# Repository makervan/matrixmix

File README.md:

# MatrixMix

Matrix mixer. Currently only 4 inputs, 4 outputs, passive. Option for passthrough sync. There's an extension port to chain mulitple mixers together, for more inputs, or add a separate amplifer for the outputs.

## License
Created by Severin Schols, and shared under CC-BY-SA-4.0. See LICENSE for more information.

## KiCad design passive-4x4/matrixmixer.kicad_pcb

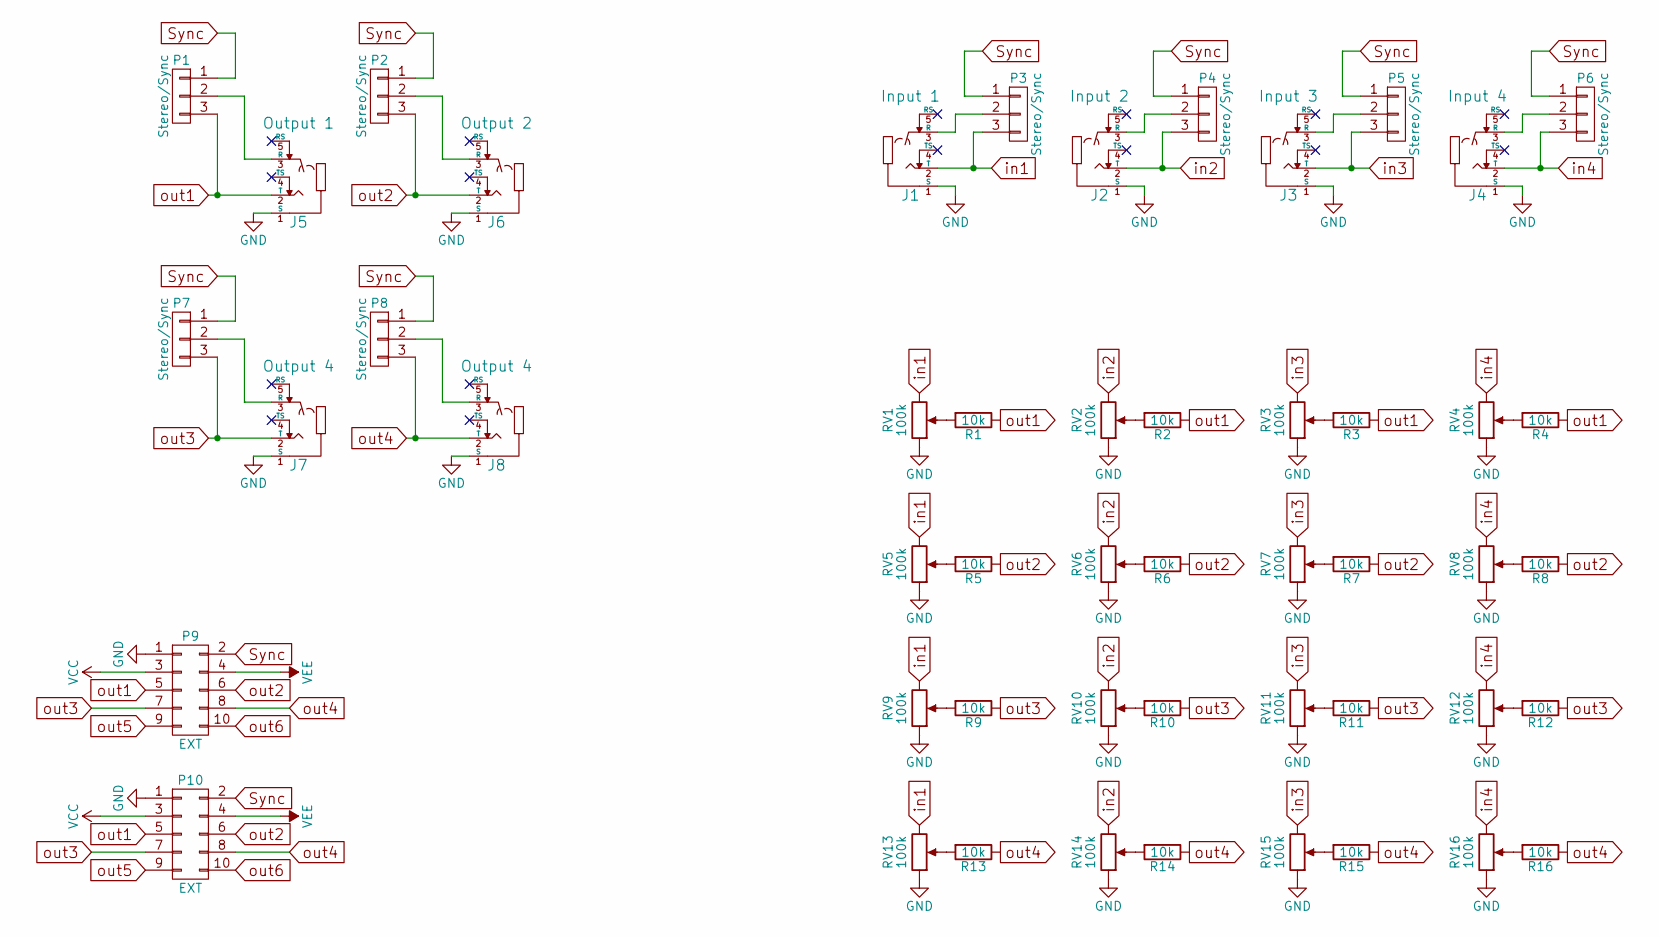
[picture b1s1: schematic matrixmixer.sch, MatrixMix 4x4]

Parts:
J1: Input 1; AudioJack3.5mm
J2: Input 2; AudioJack3.5mm
J3: Input 3; AudioJack3.5mm
J4: Input 4; AudioJack3.5mm
J5: Output 1; AudioJack3.5mm
J6: Output 2; AudioJack3.5mm
J7, J8: Output 4; AudioJack3.5mm
P1, P2, P3, P4, P5, P6, P7, P8: Stereo/Sync; Pin_Header_Straight_1x03
P9, P10: EXT; Pin_Header_Angled_2x05
R1, R2, R3, R4, R5, R6, R7, R8, R9, R10, R11, R12, R13, R14, R15, R16: 10k; Resistor_Horizontal_RM10mm
RV1, RV2, RV3, RV4, RV5, RV6, RV7, RV8, RV9, RV10, RV11, RV12, RV13, RV14, RV15, RV16: 100k; Potentiometer_Alpha-RV09

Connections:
GND: J1.1 (S), J2.1 (S), J3.1 (S), J4.1 (S), J5.1 (S), J6.1 (S), J7.1 (S), J8.1 (S), P9.1, P10.1, RV1.1, RV2.1, RV3.1, RV4.1, RV5.1, RV6.1, RV7.1, RV8.1, RV9.1, RV10.1, RV11.1, RV12.1, RV13.1, RV14.1, RV15.1, RV16.1
unnamed: J1.3 (R), P3.2
unnamed: J2.3 (R), P4.2
unnamed: J3.3 (R), P5.2
unnamed: J4.3 (R), P6.2
unnamed: J5.3 (R), P1.2
unnamed: J6.3 (R), P2.2
unnamed: J7.3 (R), P7.2
unnamed: J8.3 (R), P8.2
unnamed: R1.2, RV1.2
unnamed: R2.2, RV2.2
unnamed: R3.2, RV3.2
unnamed: R4.2, RV4.2
unnamed: R5.2, RV5.2
unnamed: R6.2, RV6.2
unnamed: R7.2, RV7.2
unnamed: R8.2, RV8.2
unnamed: R9.2, RV9.2
unnamed: R10.2, RV10.2
unnamed: R11.2, RV11.2
unnamed: R12.2, RV12.2
unnamed: R13.2, RV13.2
unnamed: R14.2, RV14.2
unnamed: R15.2, RV15.2
unnamed: R16.2, RV16.2
Sync: P1.1, P2.1, P3.1, P4.1, P5.1, P6.1, P7.1, P8.1, P9.2, P10.2
VCC: P9.3, P10.3
VEE: P9.4, P10.4
in1: J1.2 (T), P3.3, RV1.3, RV5.3, RV9.3, RV13.3
in2: J2.2 (T), P4.3, RV2.3, RV6.3, RV10.3, RV14.3
in3: J3.2 (T), P5.3, RV3.3, RV7.3, RV11.3, RV15.3
in4: J4.2 (T), P6.3, RV4.3, RV8.3, RV12.3, RV16.3
out1: J5.2 (T), P1.3, P9.5, P10.5, R1.1, R2.1, R3.1, R4.1
out2: J6.2 (T), P2.3, P9.6, P10.6, R5.1, R6.1, R7.1, R8.1
out3: J7.2 (T), P7.3, P9.7, P10.7, R9.1, R10.1, R11.1, R12.1
out4: J8.2 (T), P8.3, P9.8, P10.8, R13.1, R14.1, R15.1, R16.1
out5: P9.9, P10.9
out6: P9.10, P10.10

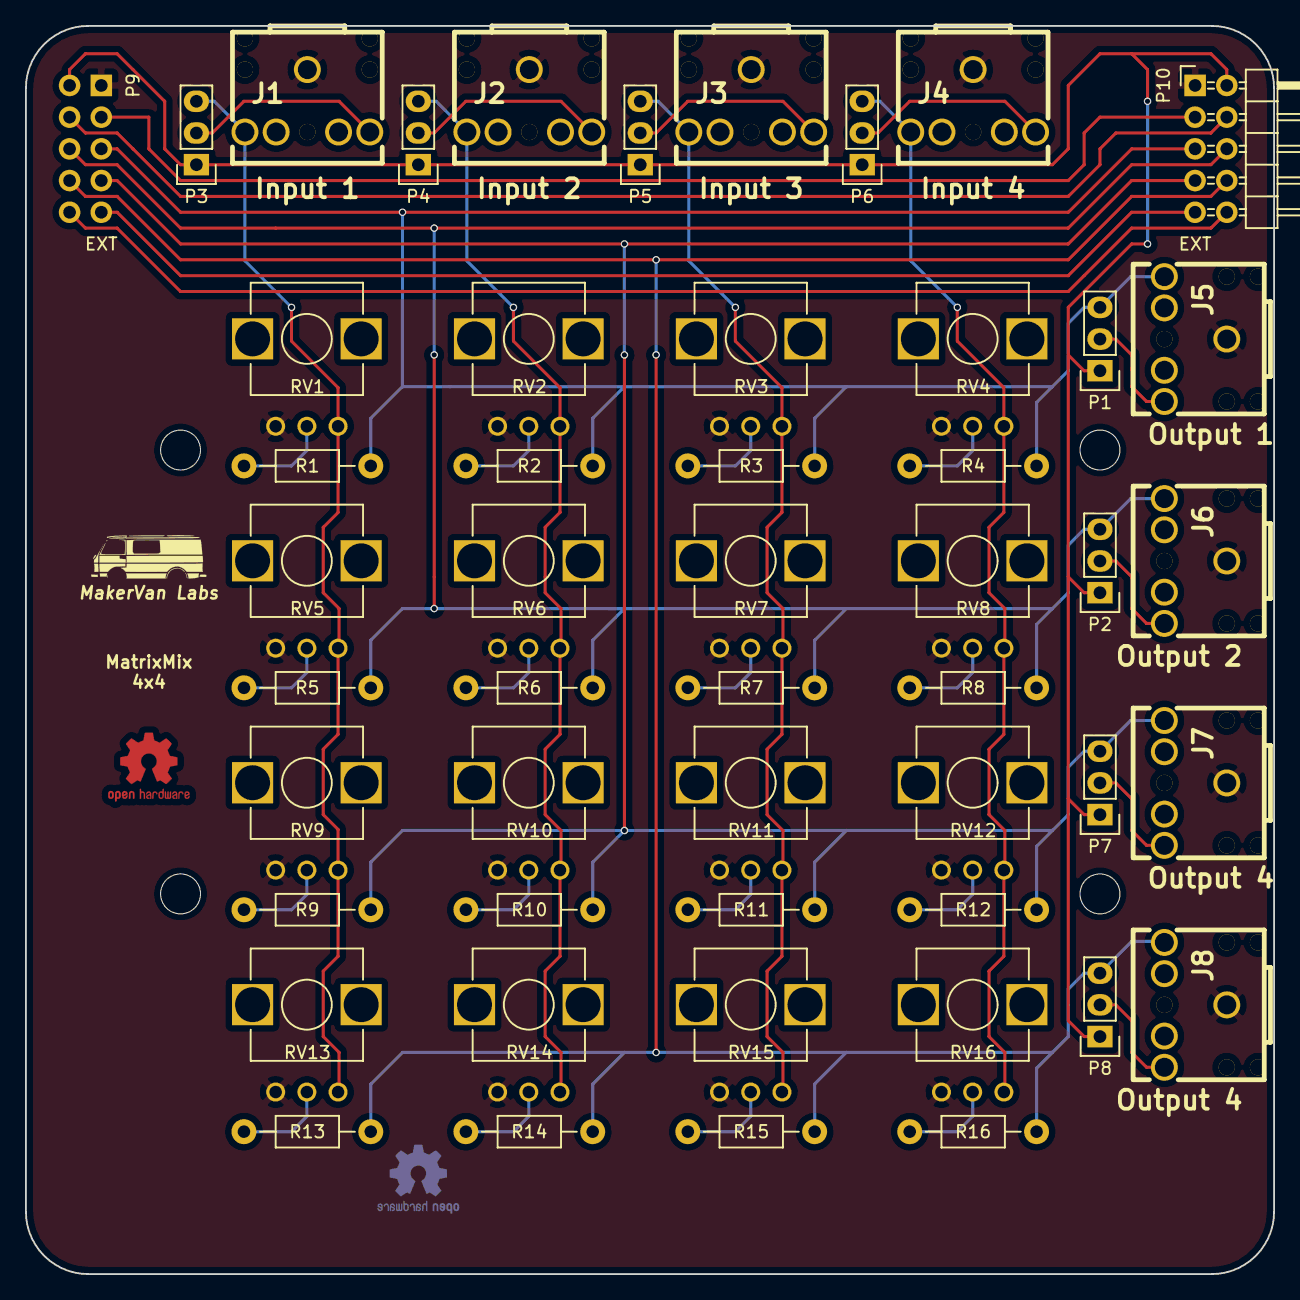
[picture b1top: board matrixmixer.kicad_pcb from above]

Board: 2 copper layers, 100.0 x 100.0 mm, 50 parts (1 on the bottom side), 38 nets.

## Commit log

2021-03-19 Passive 4x4 v0.2
2021-03-19 Lasercut front panel
2025-10-09 v3 and docs
2025-10-09 Update booklet.css
    the css was not at all good, i made it look better
2026-03-30 oshwa certification

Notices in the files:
passive-4x4/matrixmixer.kicad_pcb:
Licensed under CC BY-SA 4.0
